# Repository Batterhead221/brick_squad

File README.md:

# brick_squad (pwr_supply)

mini block breadboard pwr supply

CONCEPT DESIGN - WILL NOT FAB

A compact fixed-output breadboard power supply designed for low-current prototyping.

# brick_squad (mini_pwr_supply)

mini block pwr supply

will not fab

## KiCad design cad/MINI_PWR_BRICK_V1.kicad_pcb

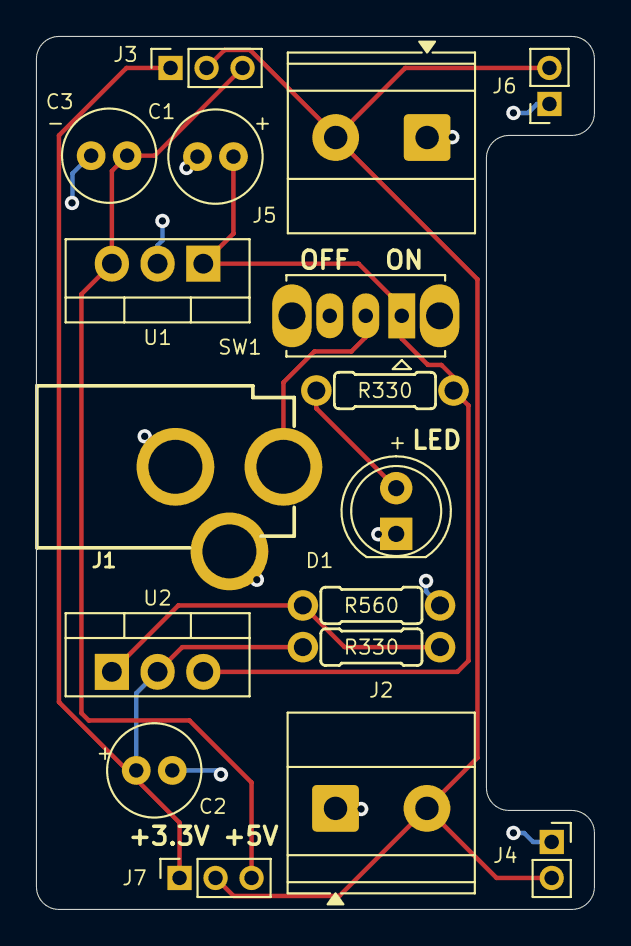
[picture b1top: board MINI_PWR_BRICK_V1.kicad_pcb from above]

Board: 2 copper layers, 31.0 x 48.5 mm, 17 parts (0 on the bottom side), 8 nets.

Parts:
C1: 10UF; C_Radial_D5.0mm_H11.0mm_P2.00mm
C2: 1UF; C_Radial_D5.0mm_H11.0mm_P2.00mm
C3: 0.1UF; C_Radial_D5.0mm_H11.0mm_P2.00mm
D1: LED; LED_D5.0mm_FlatTop
J1: Barrel_Jack_PTH
J2, J5: 3.5mm; TerminalBlock_Phoenix_MKDS-1,5-2-5.08_1x02_P5.08mm_Horizont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
J3, J7: Conn_01x03_Pin; PinSocket_1x03_P2.00mm_Vertical
J4, J6: Conn_01x02_Pin; PinSocket_1x02_P2.00mm_Vertical
R330, R330#2: 330; Resistor_14w
R560: 560; Resistor_14w
SW1: SW_SPDT; SW_Slide_SPDT_Straight_CK_OS102011MS2Q
U1: LM7805_TO220; TO-220-3_Vertical
U2: LM317_TO-220; TO-220-3_Vertical

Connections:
/+3.3V: C2.1, J3.1, J7.1, R330#2.1, U2.2 (VO)
/+5V: C3.1, J3.3, J7.3, U1.3 (VO)
/+12V: C1.1, R330.1, SW1.1 (A), U1.1 (VI), U2.3 (VI)
/PWR_IN: J1.1 (PWR), SW1.2 (B)
/PWR_OUT: J2.2, J3.2, J4.2, J5.2, J6.2, J7.2
GND: C1.2, C2.2, C3.2, D1.1 (K), J1.2 (GND), J1.3 (GNDBREAK), J2.1, J4.1, J5.1, J6.1, R560.2, U1.2 (GND)
unnamed: D1.2 (A), R330.2
unnamed: R330#2.2, R560.1, U2.1 (ADJ)

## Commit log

2026-02-15 UPDATE
    UPDATE
2026-04-18 file path restructure
2026-05-03 folder restructure
2026-05-13 Revised repo
